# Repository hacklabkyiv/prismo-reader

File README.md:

# PRISMO readers
# (WIP)

[Protocol description](./doc/protocol.md)

## Flashing instructions

Before any development mode interactions with the board it needs to be connected to a computer.
The interface intended for flashing and debugging is UART. Please connect your USB-UART adapter to the pins on the board as shown on the image below:

```
READER  USB-UART
5V  ->  5V
GND ->  GND
RX  ->  TX
TX  ->  RX
optional
3V3 ->  3V3
```

First of all the information about Micropython and it's installation can be found on their official page: [https://micropython.org/download/esp32/](https://micropython.org/download/esp32/)

Depending on your prefered OS the USB-UART can be named differently.
For example:
 - MacOS `/dev/tty.usbserial-1220`
 - Ubuntu `/dev//dev/ttyUSB0`
 - Windows `COM1`

To enter to the flashing mode the board should start with BOOT0 pin pulled to GND.
In order to achieve that short and hold BOOT pins, then short and release ENABLE pins and then release BOOT pins.

The commands also available below:
```sh
esptool.py --chip esp32 --port /dev/tty.usbserial-1220 erase_flash
```

```sh
esptool.py --chip esp32 --port /dev/tty.usbserial-1220 --baud 460800 write_flash -z 0x1000 esp32-20230426-v1.20.0.bin
```

To put source code files on board (ampy)[https://pypi.org/project/adafruit-ampy/] tool is needed.
Put all files from `src` folder to the board one by one.
> It is better for the main.py to be the last one.
>
> main.py starts processes which may affect further access to the board by `ampy` tool
> If that has happened - please enter to the REPL (`picocom` is a nice tool for that) mode and remove `main.py` manually.
> Use this prompt: `import os; os.remove('main.py')`. Don't forget to put `main.py` back in order to be back to normal operation.

```sh
ampy -p /dev/tty.usbserial-11210 -b115200 -d4 put boot.py
ampy -p /dev/tty.usbserial-11210 -b115200 -d4 put PN532.py
ampy -p /dev/tty.usbserial-11210 -b115200 -d4 put config.py
ampy -p /dev/tty.usbserial-11210 -b115200 -d4 put main.py
```
-----------
### HW test

After flashing your device, you can test your hardware. To do this, uncomment `HW_TEST` in `settings.h` file and flash this firmware. In serial monitor, with key is near the RFID frame (baudrate 9600) you should get something like this:

```
------ HW TEST STARTED --------
17:38:34.011 -> ------ HW TEST STARTED --------
17:38:37.001 -> 33384541313932323930304532333845413139323239303045323338454131393232393030453233384541313932323930304532333845413139323239303045323338454131393232393030453233384541
17:38:40.620 -> ------ HW TEST STARTED --------
17:38:43.608 -> ------ HW TEST STARTED --------

```

### Connection test with test server

Comment back `HW_TEST` in `settings.h` and specify network settings there.

```
STASSID	- name of your wifi network
STAPSK 	- password to your wifi network
HOST 	- IP address to your test server.
PORT	- Unique port of your reader
```

In `test_server.py` choose right `MY_IP` - IP of machine where `test_server.py` running and `READER_PORT`.

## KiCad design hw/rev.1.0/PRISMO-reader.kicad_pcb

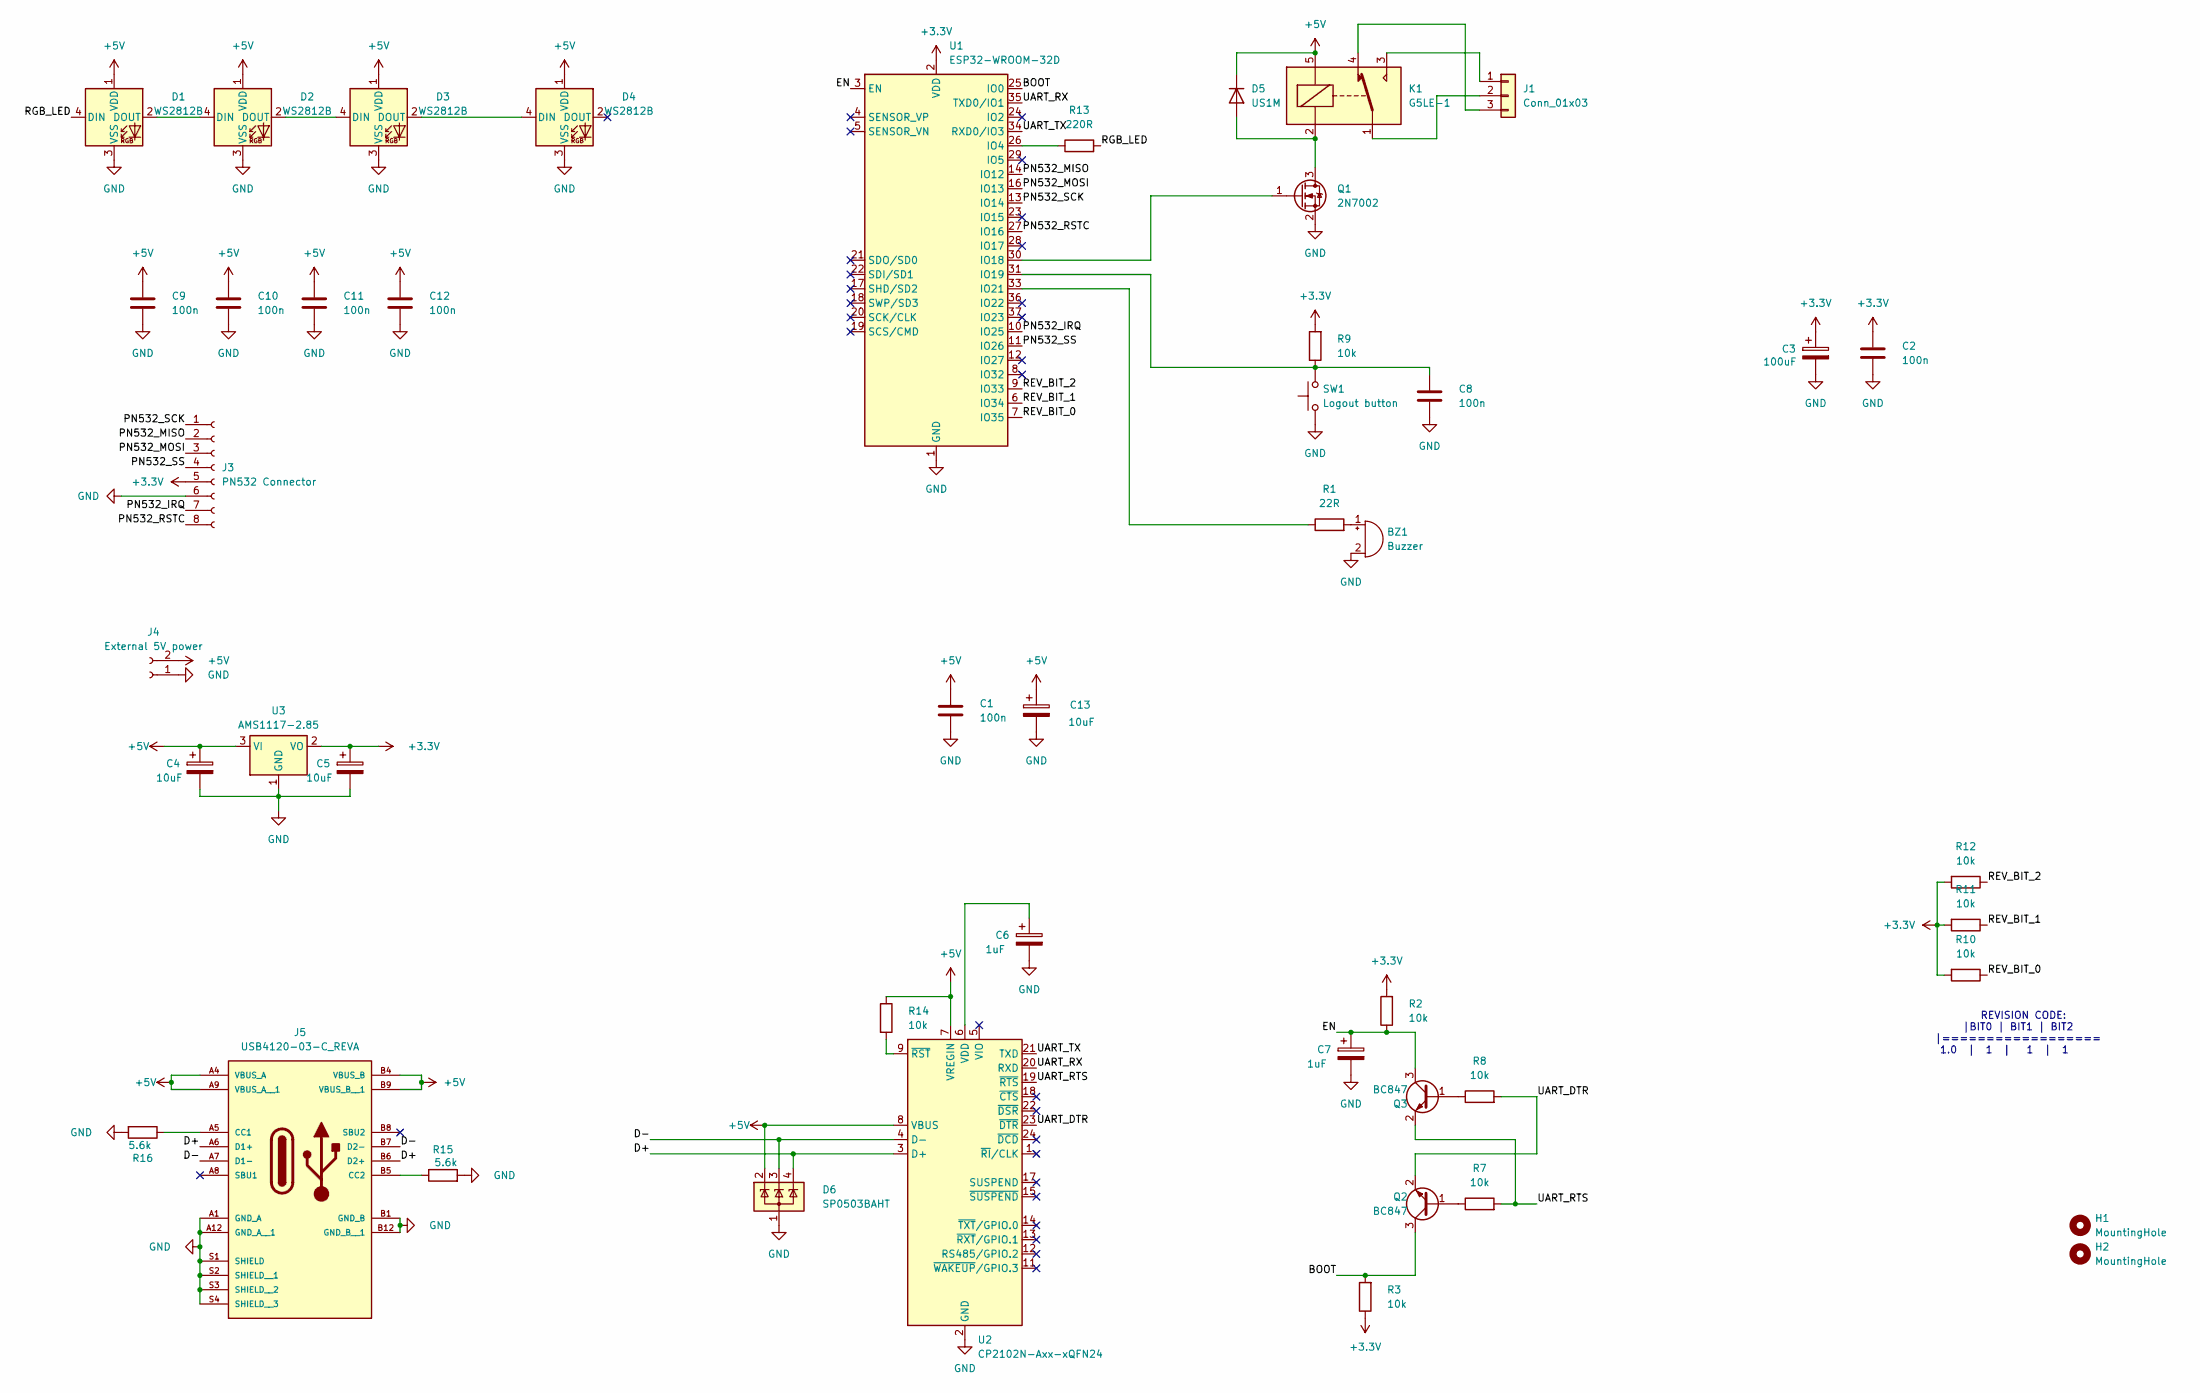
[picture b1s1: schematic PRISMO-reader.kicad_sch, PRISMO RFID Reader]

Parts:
BZ1: Buzzer; Buzzer_Murata_PKMCS0909E
C1, C2, C8, C9, C10, C11, C12: 100n; C_0805_2012Metric_Pad1.18x1.45mm_HandSolder
C3: 100uF; CP_EIA-3528-21_Kemet-B_Pad1.50x2.35mm_HandSolder
C4, C5, C13: 10uF; CP_EIA-3216-18_Kemet-A_Pad1.58x1.35mm_HandSolder
C6, C7: 1uF; C_0805_2012Metric_Pad1.18x1.45mm_HandSolder
D1, D2, D3, D4: WS2812B; LED_WS2812B_PLCC4_5.0x5.0mm_P3.2mm
D5: US1M; D_SMA
D6: SP0503BAHT; SOT-143
H1, H2: MountingHole; MountingHole_3.5mm
J1: Conn_01x03; TerminalBlock_Phoenix_PT-1,5-3-3.5-H_1x03_P3.50mm_Horizontal
J3: PN532 Connector; PinSocket_1x08_P2.54mm_Vertical_SMD_Pin1Left
J4: External 5V power; JST_XH_B2B-XH-A_1x02_P2.50mm_Vertical
J5: USB4120-03-C_REVA; GCT_USB4120-03-C_REVA
K1: G5LE-1; Relay_SPDT_Omron-G5LE-1
Q1: 2N7002; SOT-23
Q2, Q3: BC847; SOT-23
R1: 22R; R_0805_2012Metric_Pad1.20x1.40mm_HandSolder
R2, R3, R7, R8, R9, R10, R11, R12, R14: 10k; R_0805_2012Metric_Pad1.20x1.40mm_HandSolder
R13: 220R; R_0805_2012Metric_Pad1.20x1.40mm_HandSolder
R15, R16: 5.6k; R_0805_2012Metric_Pad1.20x1.40mm_HandSolder
SW1: Logout button; SW_SPST_PTS645
U1: ESP32-WROOM-32D
U2: CP2102N-Axx-xQFN24; QFN-24-1EP_4x4mm_P0.5mm_EP2.6x2.6mm
U3: AMS1117-2.85; SOT-223-3_TabPin2

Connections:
+3.3V: C2.1, C3.1, C5.1, J3.5, R2.2, R3.1, R9.2, R10.2, R11.2, R12.2, U1.2 (VDD), U3.2 (VO)
+5V: C1.1, C4.1, C9.1, C10.1, C11.1, C12.1, C13.1, D1.1 (VDD), D2.1 (VDD), D3.1 (VDD), D4.1 (VDD), D5.1 (K), D6.2 (K), J4.2, J5.A4 (VBUS_A), J5.A9 (VBUS_A__1), J5.B4 (VBUS_B), J5.B9 (VBUS_B__1), K1.5, R14.1, U2.7 (VREGIN), U2.8 (VBUS), U3.3 (VI)
/BOOT: Q2.3 (C), R3.2, U1.25 (IO0)
/D+: D6.4 (K), J5.A6 (D1+), J5.B6 (D2+), U2.3 (D+)
/D-: D6.3 (K), J5.A7 (D1-), J5.B7 (D2-), U2.4 (D-)
/EN: C7.1, Q3.3 (C), R2.1, U1.3 (EN)
/PN532_IRQ: J3.7, U1.10 (IO25)
/PN532_MISO: J3.2, U1.14 (IO12)
/PN532_MOSI: J3.3, U1.16 (IO13)
/PN532_RSTC: J3.8, U1.27 (IO16)
/PN532_SCK: J3.1, U1.13 (IO14)
/PN532_SS: J3.4, U1.11 (IO26)
/REV_BIT_0: R10.1, U1.7 (IO35)
/REV_BIT_1: R11.1, U1.6 (IO34)
/REV_BIT_2: R12.1, U1.9 (IO33)
/RGB_LED: D1.4 (DIN), R13.2
/UART_DTR: Q2.2 (E), R8.2, U2.23 (~DTR)
/UART_RTS: Q3.2 (E), R7.2, U2.19 (~RTS)
/UART_RX: U1.35 (TXD0/IO1), U2.20 (RXD)
/UART_TX: U1.34 (RXD0/IO3), U2.21 (TXD)
GND: BZ1.2 (+), C1.2, C2.2, C3.2, C4.2, C5.2, C6.2, C7.2, C8.2, C9.2, C10.2, C11.2, C12.2, C13.2, D1.3 (VSS), D2.3 (VSS), D3.3 (VSS), D4.3 (VSS), D6.1 (A), J3.6, J4.1, J5.A1 (GND_A), J5.A12 (GND_A__1), J5.B1 (GND_B), J5.B12 (GND_B__1), J5.S1 (SHIELD), J5.S2 (SHIELD__1), J5.S3 (SHIELD__2), J5.S4 (SHIELD__3), Q1.2 (S), R15.2, R16.2, SW1.1, U1.1 (GND), U1.15 (GND), U1.38 (GND), U1.39 (GND), U2.2 (GND), U2.25 (GND), U3.1 (GND)
unnamed: BZ1.1 (-), R1.2
unnamed: D1.2 (DOUT), D2.4 (DIN)
unnamed: D2.2 (DOUT), D3.4 (DIN)
unnamed: D3.2 (DOUT), D4.4 (DIN)
unnamed: D5.2 (A), K1.2, Q1.3 (D)
unnamed: J1.1, K1.3
unnamed: J1.2, K1.1
unnamed: J1.3, K1.4
unnamed: J5.A5 (CC1), R16.1
unnamed: J5.B5 (CC2), R15.1
unnamed: Q1.1 (G), U1.30 (IO18)
unnamed: Q2.1 (B), R7.1
unnamed: Q3.1 (B), R8.1
unnamed: R13.1, U1.26 (IO4)
unnamed: C8.1, R9.1, SW1.2, U1.31 (IO19)
unnamed: R1.1, U1.33 (IO21)
unnamed: C6.1, U2.6 (VDD)
unnamed: R14.2, U2.9 (~RST)

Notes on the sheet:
REVISION CODE: |BIT0 | BIT1 | BIT2 |================== 1.0 | 1 | 1 | 1

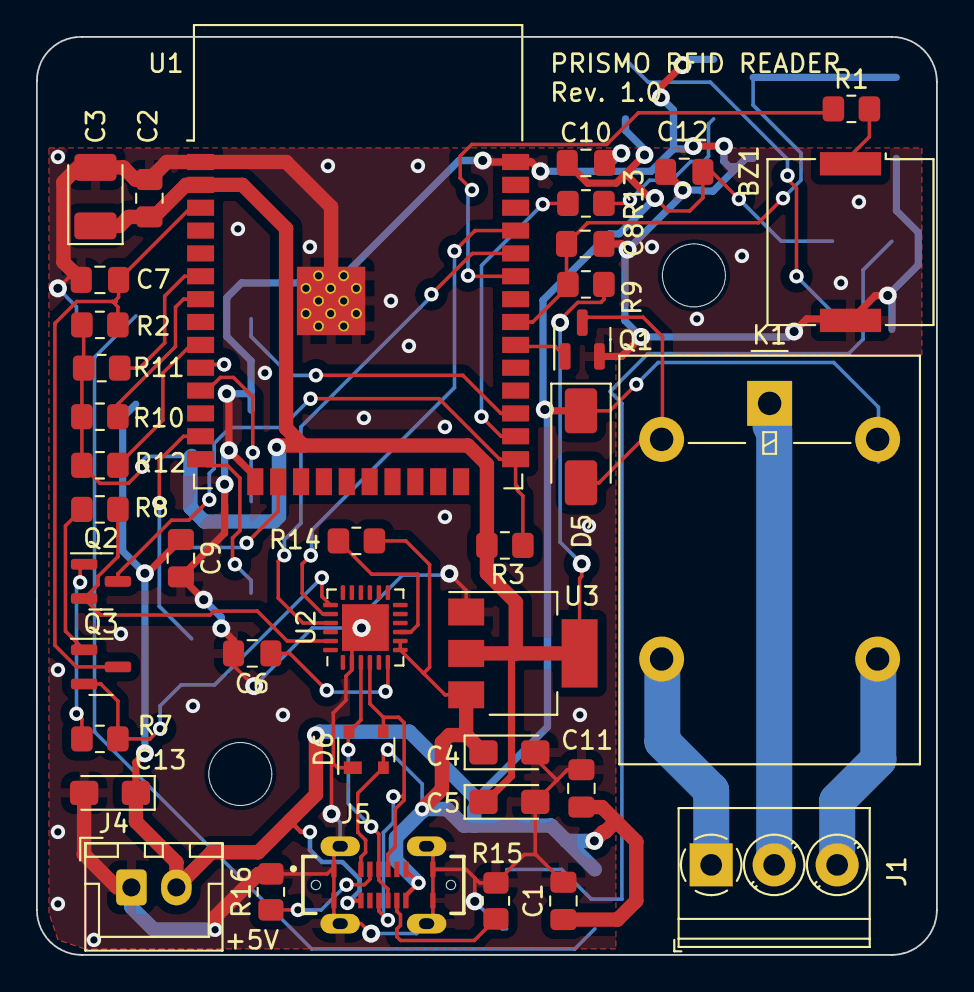
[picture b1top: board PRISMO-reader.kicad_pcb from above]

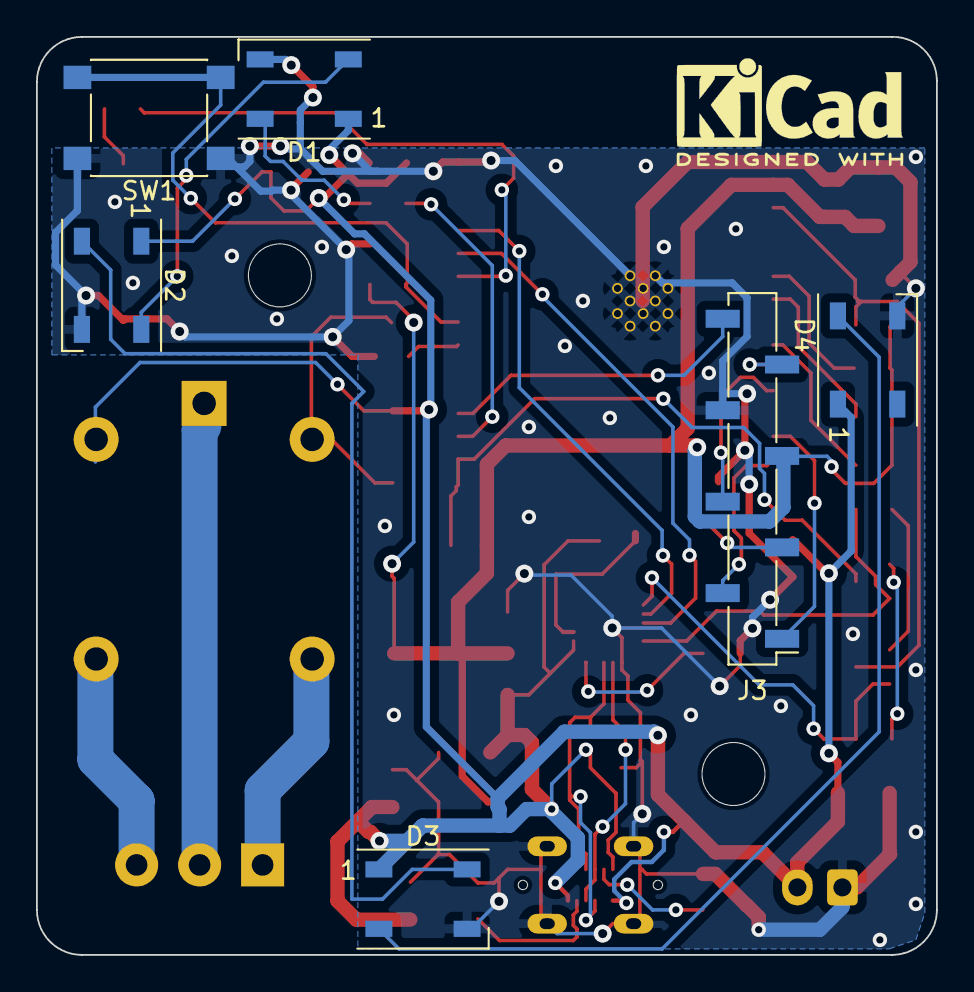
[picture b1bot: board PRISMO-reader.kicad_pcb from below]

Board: 2 copper layers, 50.0 x 51.0 mm, 47 parts (6 on the bottom side), 39 nets.

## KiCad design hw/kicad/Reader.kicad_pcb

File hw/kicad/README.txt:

This KiCad project was generated from Altium Designer.
No errors or warnings or any difficulties appeared.

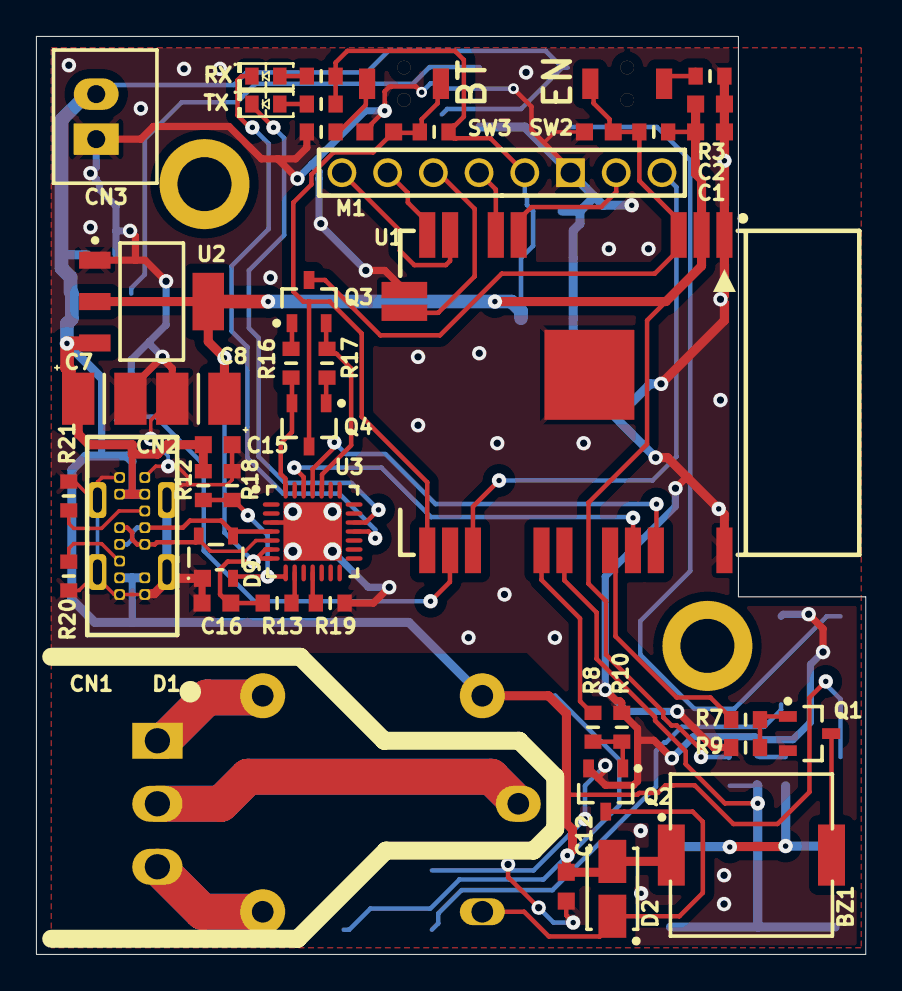
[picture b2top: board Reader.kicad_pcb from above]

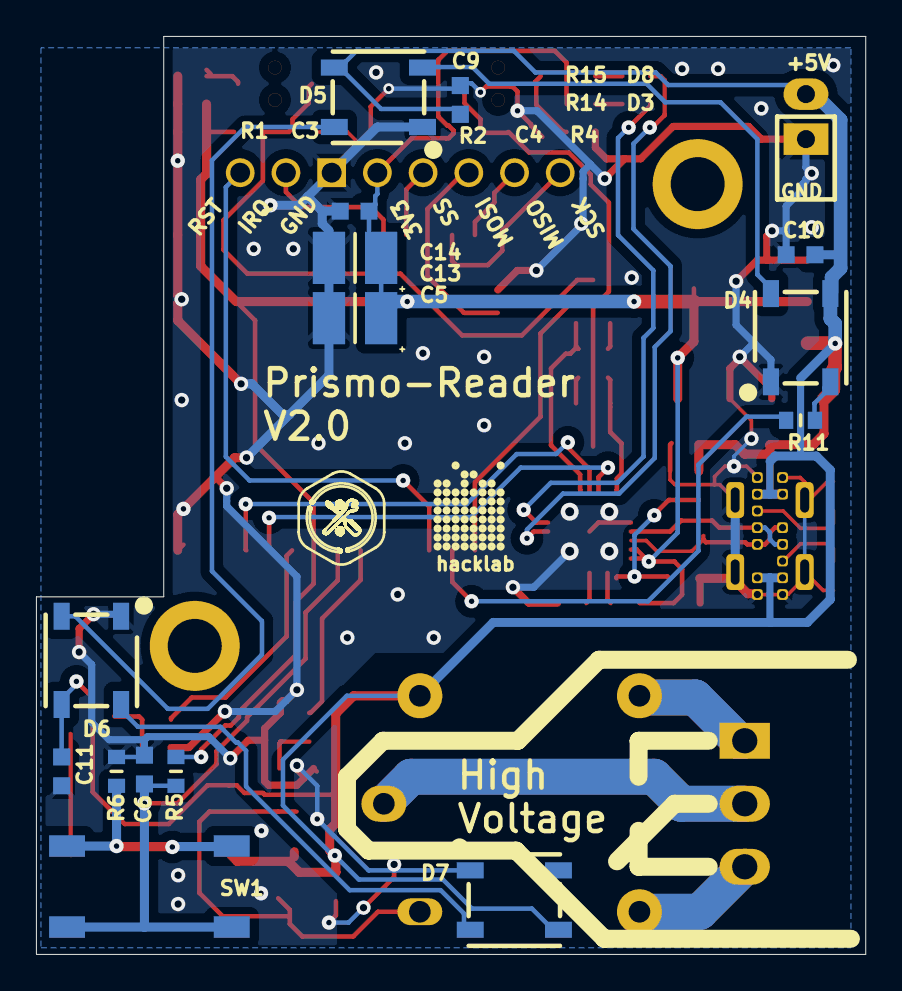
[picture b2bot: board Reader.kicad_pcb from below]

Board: 2 copper layers, 46.1 x 51.0 mm, 61 parts (15 on the bottom side), 43 nets.

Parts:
BZ1: MSC_BUZZER; _04_Database_DSW_Lib.DbLib/MSC_MSC_MURATA_PKMCS0909E4000-R1
C1, C2, C3, C4, C6, C9, C10, C11, C12, C14, C15, C16: CAP; _04_Database_DSW_Lib.DbLib/CAP_CAPC1608X87N
C5, C13: CAP_POL; _03_Models_02_Footprints_01_Footprint_SMT_02_IPC-7352 Discr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
C7, C8: CAP_POL; _04_Database_DSW_Lib.DbLib/CAP_CAPM3528x210_N
CN1: CN_1X3M; _04_Database_DSW_Lib.DbLib/CN_CN_Wurth_691322110003
CN2: CN_USB-C; _04_Database_DSW_Lib.DbLib/CN_CN_USB-C_vertical
CN3: CN_1X2M; _04_Database_DSW_Lib.DbLib/CN_CN_XH2.54-2P-MALE
D1: MSC_5pin_Relay; _03_Models_02_Footprints_04_Misc_MSC_SRD-12VDC-SL-C.PcbLib_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
D2: DIO; DO-214AC
D3, D8: DIO_LED; _04_Database_DSW_Lib.DbLib/DIO_DIO_RED_0603
D4, D5, D6, D7: DIO_LED_WS2812_5050; _03_Models_02_Footprints_04_Misc_DIO_LED_WORLDSEMI_WS2812B.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
D9: DIO_TVS_THREE; _03_Models_02_Footprints_01_Footprint_SMT_SIMPLE_SOT143.Pcb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
M1: MOD_RFID_NFC_PN532; _04_Database_DSW_Lib.DbLib/MSC_MOD_RFID_NFC_PN532_no3d
Q1, Q2, Q3, Q4: TRS_NPN_123; _03_Models_02_Footprints_01_Footprint_SMT_SIMPLE_SOT23.PcbL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
R1, R2, R3, R4, R5, R6, R7, R8, R9, R10, R11: RES; _04_Database_DSW_Lib.DbLib/RES_RESC1608X55N
R12, R13, R14, R15, R16, R17, R18, R19, R20, R21: RES; _03_Models_02_Footprints_01_Footprint_SMT_02_IPC-7352 Discr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
SW1: Tact_Switch; _03_Models_02_Footprints_04_Misc_Tact_Switch.PcbLib_Tact_Sw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
SW2, SW3: Tact_Switch_2pin; _03_Models_02_Footprints_04_Misc_MSC_KLS7-TS3401.PcbLib_MSC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
U1: MSC_ESP32-WROOM-32D; _03_Models_02_Footprints_01_Footprint_SMT_11_MSC Miscellane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
U2: IC_TI_LM1117; _03_Models_02_Footprints_01_Footprint_SMT_03_IPC-7353 GullW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
U3: IC_SILICON_LABS_CP2102N-GQFN28; _03_Models_02_Footprints_01_Footprint_SMT_SIMPLE_QFN-28.Pcb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

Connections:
3V3: C1.2, C2.2, C5.1, C8.1, C13.1, C14.2, C16.2, M1.9, R1.2, R2.2, R5.2, R13.2, R14.2, R15.2, U1.2, U2.2, U2.4, U3.6, U3.7
5V: BZ1.1, C7.1, C9.2, C10.2, C11.2, C12.2, C15.2, CN2.2, CN2.7, CN2.22, CN2.77, CN3.2, D1.1, D2.1, D4.1, D5.1, D6.1, D7.1, R12.2, U2.3
BOOT: C4.2, Q4.3, R2.1, SW3.2, U1.25
D+: CN2.4, CN2.44, D9.3, U3.4
D-: CN2.5, CN2.55, D9.4, U3.5
EN: C3.2, Q3.3, R1.1, SW2.2, U1.3
GND: C1.1, C2.1, C3.1, C4.1, C5.2, C6.1, C7.2, C8.2, C9.1, C10.1, C11.1, C12.1, C13.2, C14.1, C15.1, C16.1, CN2.1, CN2.8, CN2.11, CN2.88, CN2.Z, CN3.1, D4.3, D5.3, D6.3, D7.3, D9.1, M1.10, Q1.2, Q2.2, R3.1, R4.1, R6.1, R9.1, R10.1, R18.1, R19.1, R20.1, R21.1, U1.1, U1.15, U1.38, U1.39, U2.1, U3.3, U3.29
LOGOUT: C6.2, R5.1, SW1.3, SW1.4, U1.31
NetBZ1_2: BZ1.2, Q1.3
NetCN2_3: CN2.3, R21.2
NetCN2_33: CN2.33, R20.2
NetD1_3: D1.3, D2.2, Q2.3
NetD3_2: D3.2, R14.1
NetD4_2: D4.2, D5.4
NetD4_4: D4.4, R11.2
NetD5_2: D5.2, D6.4
NetD6_2: D6.2, D7.4
NetD8_2: D8.2, R15.1
NetD9_2: D9.2, R12.1, R18.2, U3.8
NetQ1_1: Q1.1, R7.2, R9.2
NetQ2_1: Q2.1, R8.2, R10.2
NetQ3_1: Q3.1, R16.2
NetQ4_1: Q4.1, R17.2
NetR3_2: R3.2, SW2.1
NetR4_2: R4.2, SW3.1
NetR6_2: R6.2, SW1.1, SW1.2
NetR13_1: R13.1, U3.9
NetR19_2: R19.2, U3.11
RGB-LED: R11.1, U1.26
SPI_IRQ: M1.11, U1.10
SPI_MISO: M1.6, U1.14
SPI_MOSI: M1.7, U1.16
SPI_RST: M1.12, U1.27
SPI_SCK: M1.5, U1.13
SPI_SS: M1.8, U1.11
UART_DTR: Q4.2, R16.1, U3.28
UART_RTS: Q3.2, R17.1, U3.24
UART_RX_LED: D8.1, U3.18
UART_Rx: U1.34, U3.26
UART_TX_LED: D3.1, U3.19
UART_Tx: U1.35, U3.25
buzzer: R7.1, U1.33
relay: R8.1, U1.30

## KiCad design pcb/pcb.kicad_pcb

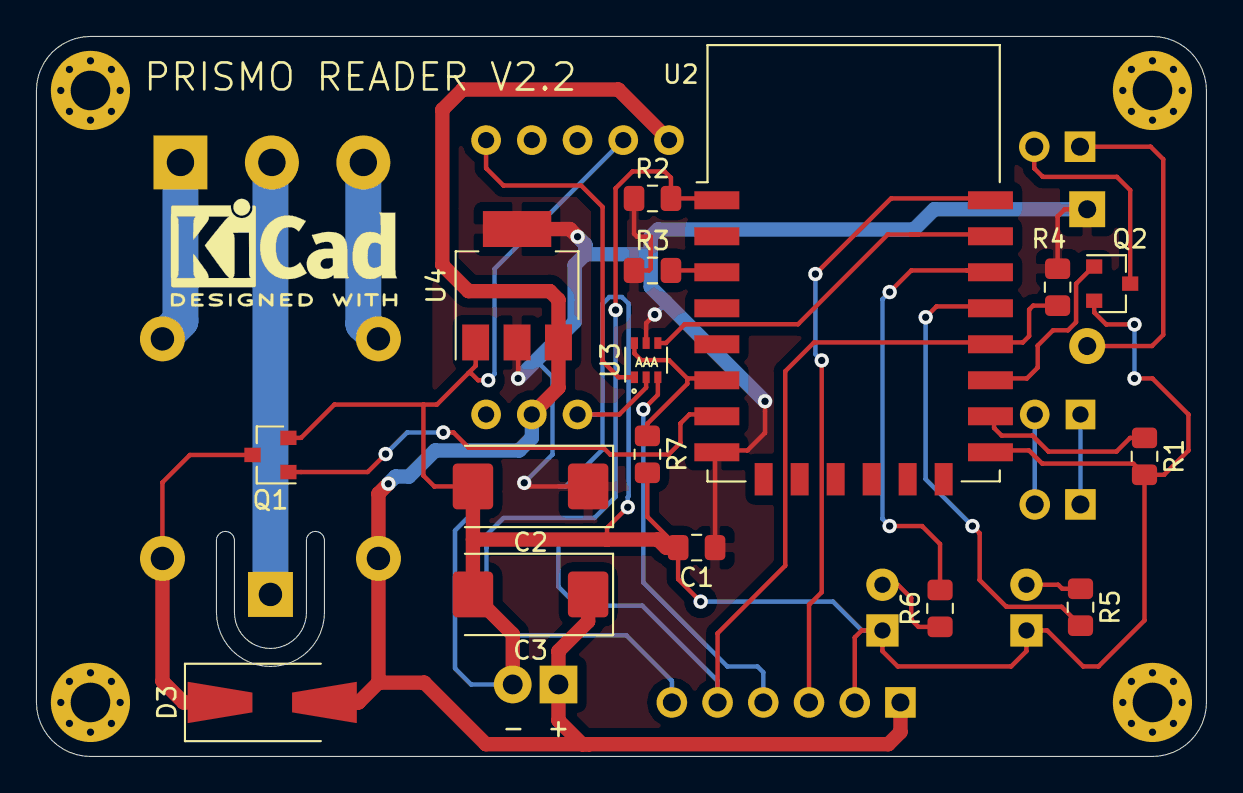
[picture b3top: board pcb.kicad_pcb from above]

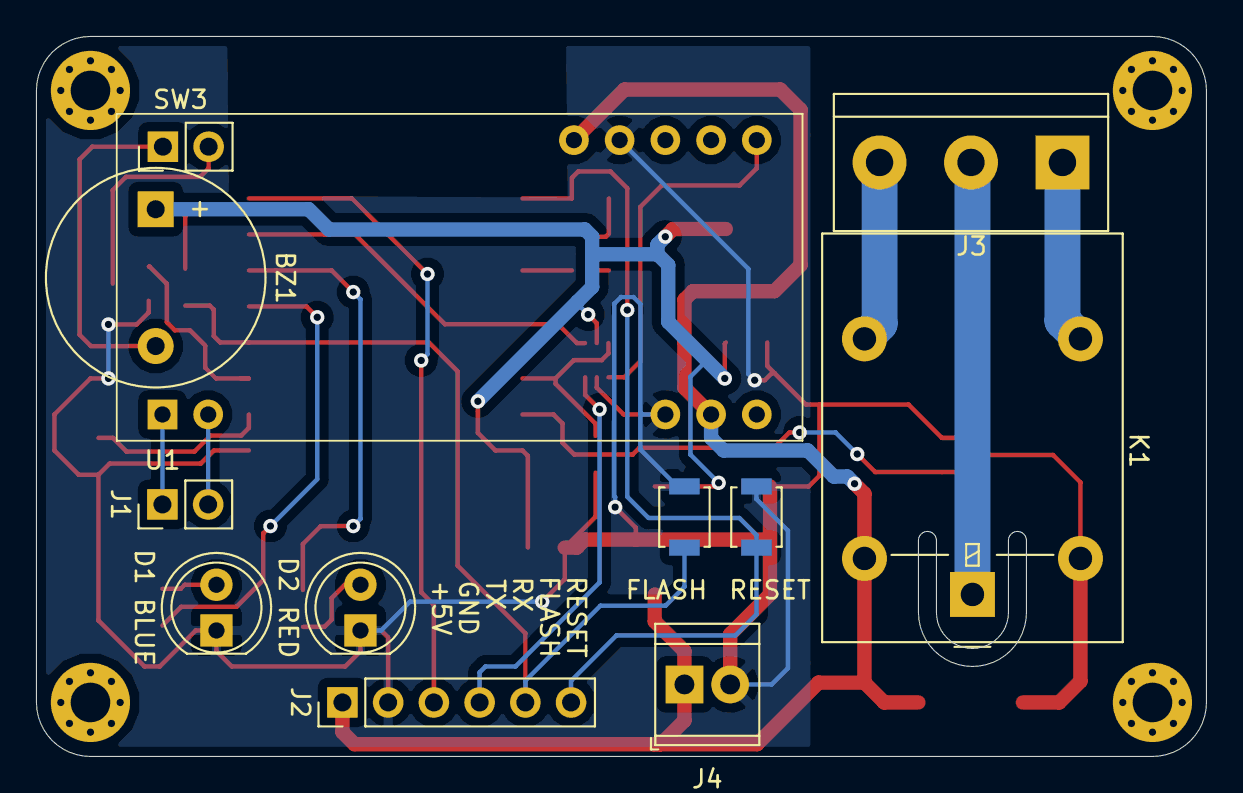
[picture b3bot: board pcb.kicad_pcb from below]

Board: 2 copper layers, 65.0 x 40.0 mm, 32 parts (12 on the bottom side), 26 nets.

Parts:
 : MountingHole_2.2mm_M2_Pad_Via
 #2,  #3,  #4: MountingHole_2.2mm_M2_Pad_Via
BZ1: Buzzer; Buzzer_12x9.5RM7.6
C1: 100n; C_0805_2012Metric_Pad1.15x1.40mm_HandSolder
C2, C3: 100uF; CP_EIA-7343-31_Kemet-D_Pad2.25x2.55mm_HandSolder
D1 BLUE, D2 RED: LED; LED_D5.0mm_FlatTop
D3: GS1M; D_SMA-SMB_Universal_Handsoldering
FLASH: Flash; SW_SPST_B3U-1000P
J1: Conn_01x02; PinHeader_1x02_P2.54mm_Vertical
J2: Conn_01x06; PinHeader_1x06_P2.54mm_Vertical
J3: Load connect; TerminalBlock_bornier-3_P5.08mm
J4: Screw_Terminal_01x02; TerminalBlock_TE_282834-2_1x02_P2.54mm_Horizontal
K1: G5LE-1; Relay_SPDT_Omron-G5LE-1
Q1, Q2: 2N7002; SOT-23
R1, R2, R3, R4, R7: 10k; R_0805_2012Metric_Pad1.15x1.40mm_HandSolder
R5, R6: 200; R_0805_2012Metric_Pad1.15x1.40mm_HandSolder
RESET: Reset; SW_SPST_B3U-1000P
SW3: SW_DIP_x01; PinHeader_1x02_P2.54mm_Vertical
U1: RDM6300; RDM6300_B38.5x18.2mm
U2: ESP-12E
U3: NC7SB3157P6X; SOT-363_SC-70-6
U4: LD1117S33TR_SOT223; SOT-223-3_TabPin2

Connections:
+3V3: BZ1.1, C1.1, C2.1, R2.1, R3.1, R4.1, U2.8, U3.5, U4.2
+5V: C3.1, D3.2, J2.1, J4.1, K1.5, U1.4, U1.10, U4.3
/BUZZER: Q2.1, U2.17
/RX: U1.6, U3.1
GND: C1.2, C2.2, C3.2, D1 BLUE.1, D2 RED.1, FLASH.2, J2.2, J4.2, Q1.2, Q2.2, R1.2, R7.2, RESET.1, U1.3, U1.9, U2.15, U3.2, U4.1
unnamed: BZ1.2, SW3.1
unnamed: D1 BLUE.2, R5.1
unnamed: D2 RED.2, R6.1
unnamed: D3.1, K1.2, Q1.3
unnamed: J1.1, U1.1
unnamed: J1.2, U1.2
unnamed: J2.3, U2.22
unnamed: J2.4, U3.3
unnamed: FLASH.1, J2.5, R4.2, U2.18
unnamed: J2.6, R2.2, RESET.2, U2.1
unnamed: J3.1, K1.3
unnamed: J3.2, K1.1
unnamed: J3.3, K1.4
unnamed: Q1.1, U2.7
unnamed: Q2.3, SW3.2
unnamed: R1.1, U2.16
unnamed: R3.2, U2.3
unnamed: R5.2, U2.19
unnamed: R6.2, U2.20
unnamed: R7.1, U2.6, U3.6
unnamed: U2.21, U3.4

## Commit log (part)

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2020-02-14 PCB: Added very first version
2020-02-26 Preliminary version of firmware
2020-02-26 Added test server for basic test
2020-02-26 Updated README with new instructions
2020-02-28 Some impromevents
    - GPIO15 should be connected to GND
    - Buzzer connected through transistor
    - Buzzer can be disabled with switch(because it enables during flashing, which is annoying)
    - Smaller terminal block for power connector
2020-02-28 Different optimizations
2020-05-22 GPIO9 and GPIO10 should be not used, fix this
    we cannot use these pins because they are internally connected to SPI
    flash memory.
2020-06-05 Firmware: Switch to PlatformIO
2020-06-19 Server: Initial version of async server
2020-06-19 Firmware: Refactor and bug fixes
2020-09-17 Dump changes from working machine
2020-12-12 Fix access and slack notification
2023-06-03 Move to ESP32 and Gwiot7941e reader
2023-06-03 Add write logs to database and update .gitignore
2023-06-08 Modify test server to either grant or deny access
2023-06-08 Micropython firmware fix version
2023-06-08 Basic logic of the reader, together with config and PN532 abstraction module
2023-06-08 Attach hardware design repo as a submodule
2023-06-10 Adjusted interfaces according to the real server
2023-06-12 Updated hardware
2023-07-02 Correct pins according to the manufactured board
2023-07-02 Flashing instructions and ilustrations
2023-07-26 Read on interrupt instead of the timer
    Increase timeout from 500 to 5000 (5sec), due to library for PN532
    specifics.
    Once the read method is called it tries to read every timeout q-ty
    of time.
    In order to make it read on interrupt also the timeout is increased
    to a huge amount of time.
2023-07-26 Light indication while connecting to the Wi-Fi network
2023-10-14 Offline user search and access resolution
2023-10-28 Different changes:
    * Add fetching of allowed keys from server
    * Local key storage
    * Code formatting (autopep8)
2023-11-01 Trying to allow offline work
    There are still some bug when device hangs or reboots when network
    request failed. Need more QA!
2023-11-01 Fix bug with reboot and code refactoring
    * Fixed bug with simultaneous reboot after GET request - moved logic
    from IRQ to polling mode
    * Code refactoring
    * Beep control because my cat Cherry asks me to turn off this sound!
2023-11-02 Add ping before any requests performed
    Inside requests module, sockets are used in blocking mode and current
    implementation of LWIP of ESP32 does not support timeouts. This leads
    to long timeouts when host is unreachable and this blocks work of whole
    reader. As workaround quick ping in polling mode was added before any
    requests are performed.
2023-11-07 Updated according to new API
2023-11-20 Some changes
2023-11-29 Update api and more check on PN532
2023-12-04 Fix problem with JSON payload in POST request
    Wrong payload type in post request during reporting of
    tool usage leads to blowing mind of prismo server.
2023-12-08 Updated micropython firmware
2023-12-13 Changed CS pin, logout button and flasher script
2023-12-13 Store reader-specific settings in json file
2023-12-13 Make flasher script more readable by ffrontend
2023-12-18 Flasher script and logic refactored
2024-01-12 Make flasher script suitable to run in docker
2024-01-12 Another small tune for docker: use system esptool utility
2024-01-13 Use relative path to FW
2024-01-13 Version 2.0 hardware + KiCad
2024-01-17 Path changed
2024-01-17 Files updated
2024-01-17 Fixes to make board suitable for local manucatruing
    - Track made 0.2 min
    - Pads 0.2 min(CP2102)
    - Another bug fixes...
2024-02-04 Some changes for new HW revision
2024-02-04 Some changes to work with new HW
2024-02-05 Change port to production version
2024-02-05 Change port to production version (#13)
2024-02-10 Bugfixes and improvements
    * Relay was inverted:))
    * Enabled watchdog
    * Logout button support
2024-02-10 Add door type of reader
2024-02-10 Support new type of device: door
2024-02-10 Rev 1.0 of reader added
2024-03-10 Removed old versions
2024-07-05 Fixed problem with wrong VBUS connection of USB port
2025-05-23 fixed CP2102 peripheral connection
2025-05-23 renamed leds in order of connection
2025-06-03 Bugfix with CP2102 connection (#15)
    * fixed CP2102 peripheral connection
    * renamed leds in order of connection
2025-06-03 Updated gerber files to most recent version
2025-06-26 - moved relay position on a few mm - fixed hostname configuration - deleted wifi connection timeout - decreased watchdog period
2025-07-29 Create README.md
    3d model files for printing the reader shells for outdoor and indoor use
2025-07-29 3d models for reader shells
    a set of 3d models for printing reader shells for indoor and doutdoor use
2025-12-13 - massive code refactor - fixed led animation on booting - checked and wrapped by try/except all places where use external module and network - checked timeouts on network communication - added new m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
2025-12-19 - added PM523 healthcheck and force reset reader in background thread
2025-12-20 Refactoring coding base (#16)
    * fixed CP2102 peripheral connection
    * renamed leds in order of connection
    * - moved relay position on a few mm
    - fixed hostname configuration
    - deleted wifi connection timeout
    - decreased watchdog period
2026-05-15 version name update
